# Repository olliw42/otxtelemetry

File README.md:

**LEGACY LEGACY LEGACY**

**This repository is legacy and deprecated.**

Please see https://github.com/olliw42/mTX for the current location of the project and the OlliW Telemetry for mTx Lua script.

-----------

OlliW Telemetry for OpenTx/EdgeTx with MAVLink, Lua Scripts, Hardware, Code and Stuff
===========

The project brings native MAVLink telemetry capabilities to OpenTx.

Project home page: http://www.olliw.eu/2020/olliwtelem

Discussion thread at rcgroups: https://www.rcgroups.com/forums/showthread.php?3532969-MAVLink-for-OpenTx-and-Telemetry-Script

## Lua Widget Scripts: Installation

The latest telemetry script works with OpenTx (for EdgeTx only "older" firmwares/scripts are available).

For the moment please visit the project web page for descriptions, or better, join the discussion thread.

## External Transmitter Bay MAVLink Bridge

For the moment please visit the discussion thread.

## Licence

GPL v3

## Acknowledgements

The design of the autopilot page is much inspired by the Yaapu Telemetry script. (https://github.com/yaapu/FrskyTelemetryScript)

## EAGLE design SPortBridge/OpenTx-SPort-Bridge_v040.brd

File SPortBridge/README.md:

OlliW Telemetry for OpenTx/EdgeTx with MAVLink: SPort Bridge
===========

The SPort Bridge translates between the bi-directional one-wire communication signal on the SPort pin and the normal bi-directional two-wire (Tx, Rx) UART signals.

Hardware-wise this requires two functional units, a unit which is doing the splicing from one to two and also inverts the signals, and a microprocessor which decodes/encodes the signal on the one-wire line. 

Comment: The principle is not new at all and widley used. It is e.g. also used in the MPM (multi protocol module) or Siyi FM30 (which just copied it from MNM).

Comment: Microcontroller exist which do provide the slice&invert function internally, which would allow a significantly reduced scheme. The STM32F103, which I use here, does not have that, hence the extra "chicken fat", but I use it since it is also used in the Siyi FM30 transmitter module, which is an excellent commercially available and reasonably priced hardware platform for our purposes. So, the PCB here is actually kind of a development platform for that.

The PCB can be populated such that it exactly reproduces the splicing/inverting unit as used in the MPM and Siyi FM30 (which is normally high level), but it also can be populated such that it is more appropriate for a normally low signal like the one on the SPort (I use that scheme).

The microcontroller needs to be loaded with code, an example C code is provided (you need to spice it up with what it needs to build it).

Comment: I would have loved to provide an Arduino sketch, since this would be really the easiest for most, but I could not figure out how to call low level CMSIS functions in this framework. MAybe some can provide an example or help me out with this.

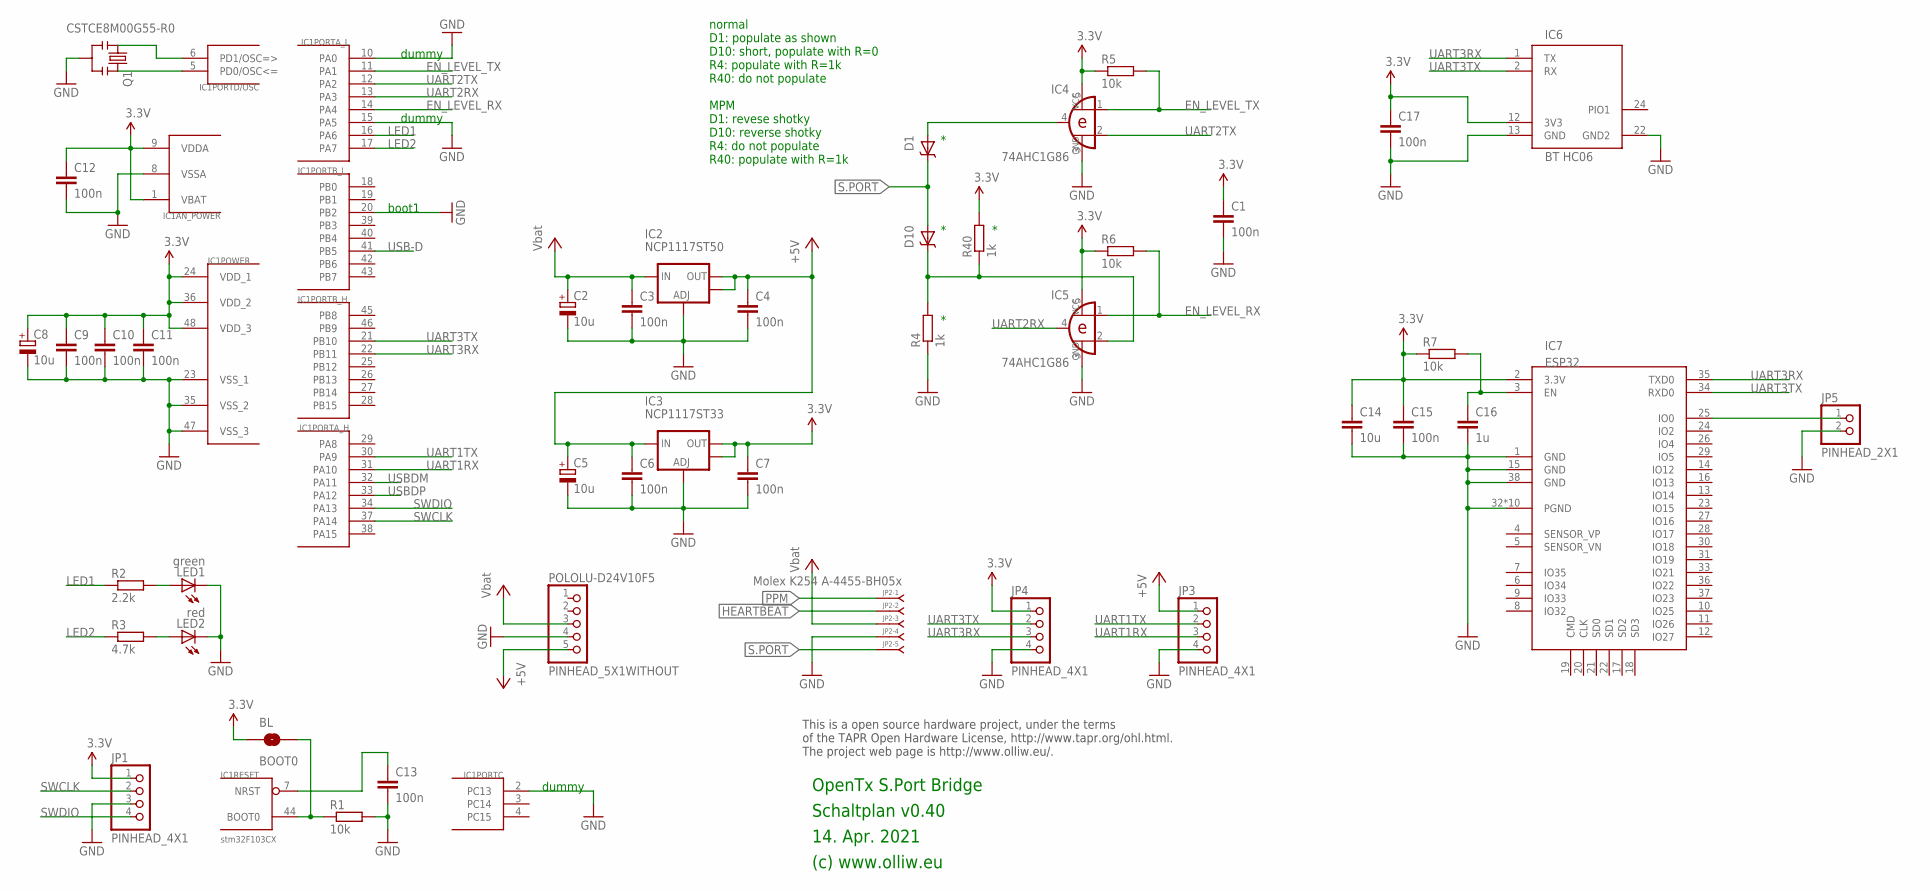
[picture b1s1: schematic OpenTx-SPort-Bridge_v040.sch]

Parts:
BL: BOOT0; SJ_2S-NO
C1, C3, C4, C6, C7, C9, C10, C11, C12, C13, C15, C17: 100n; C0603
C2, C5, C8: 10u; SMC_A
C14: 10u; C0805
C16: 1u; C0603
D1, D10: PMEG3010ER; SOD123W-DIODE
IC1: stm32F103CX; TQFP48
IC2: NCP1117ST50; SOT223
IC3: NCP1117ST33; SOT223
IC4, IC5: 74AHC1G86; SOT23-5-VER1
IC6: BT HC06; BT_HC05_BASIC
IC7: ESP32; ESP-WROOM-32D
JP1, JP3, JP4: PINHEAD_4X1
JP2: Molex K254 A-4455-BH05x; 4455-B05
JP5: PINHEAD_2X1
LED1: green; LED3MM
LED2: red; LED3MM
POLOLU-D24V10F5: PINHEAD_5X1WITHOUT; PINHEAD_5X1_WO
Q1: CSTCE8M00G55-R0; RESONATOR-SMD
R1, R5, R6, R7: 10k; R0603
R2: 2.2k; R0603
R3: 4.7k; R0603
R4, R40: 1k; R0603

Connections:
3.3V: BL.1, C1.1, C7.1, C8.+, C9.1, C10.1, C11.1, C12.1, C14.1, C15.1, C17.1, IC1.1 (VBAT), IC1.9 (VDDA), IC1.24 (VDD_1), IC1.36 (VDD_2), IC1.48 (VDD_3), IC3.2 (OUT), IC3.4 (OUT), IC4.5 (VCC), IC5.5 (VCC), IC6.12 (3V3), IC7.2 (3.3V), JP1.1, JP4.1, R5.1, R6.1, R7.1, R40.2
+5V: C4.1, C5.+, C6.1, IC2.2 (OUT), IC2.4 (OUT), IC3.3 (IN), JP3.1, POLOLU-D24V10F5.5
BOOT0: BL.2, IC1.44 (BOOT0), R1.1
EN_LEVEL_RX: IC1.14 (PA4), IC5.1 (I0), R6.2
EN_LEVEL_TX: IC1.11 (PA1), IC4.1 (I0), R5.2
GND: C1.2, C2.-, C3.2, C4.2, C5.-, C6.2, C7.2, C8.-, C9.2, C10.2, C11.2, C12.2, C13.2, C14.2, C15.2, C16.2, C17.2, IC1.2 (PC13), IC1.8 (VSSA), IC1.10 (PA0), IC1.15 (PA5), IC1.20 (PB2), IC1.23 (VSS_1), IC1.35 (VSS_2), IC1.47 (VSS_3), IC2.1 (ADJ), IC3.1 (ADJ), IC4.3 (GND), IC5.3 (GND), IC6.13 (GND), IC6.22 (GND2), IC7.1 (GND), IC7.15 (GND), IC7.32 (PGND), IC7.38 (GND), IC7.39 (PGND), IC7.40 (PGND), IC7.41 (PGND), IC7.42 (PGND), IC7.43 (PGND), IC7.44 (PGND), IC7.45 (PGND), IC7.46 (PGND), IC7.47 (PGND), JP1.3, JP2.4, JP3.4, JP4.4, JP5.2, LED1.K (C), LED2.K (C), POLOLU-D24V10F5.4, Q1.2, R1.2, R4.1
HEARTBEAT: JP2.2
LED1: IC1.16 (PA6), R2.1
LED2: IC1.17 (PA7), R3.1
unnamed: IC7.25 (IO0), JP5.1
unnamed: C16.1, IC7.3 (EN), R7.2
unnamed: D10.C, IC5.2 (I1), R4.2, R40.1
unnamed: D1.A, IC4.4 (O)
unnamed: C13.1, IC1.7 (NRST)
unnamed: LED1.A, R2.2
unnamed: LED2.A, R3.2
unnamed: IC1.5 (PD0/OSC<=), Q1.3
unnamed: IC1.6 (PD1/OSC=>), Q1.1
PPM: JP2.1
S.PORT: D1.C, D10.A, JP2.5
SWCLK: IC1.37 (PA14), JP1.2
SWDIO: IC1.34 (PA13), JP1.4
UART1RX: IC1.31 (PA10), JP3.3
UART1TX: IC1.30 (PA9), JP3.2
UART2RX: IC1.13 (PA3), IC5.4 (O)
UART2TX: IC1.12 (PA2), IC4.2 (I1)
UART3RX: IC1.22 (PB11), IC6.1 (TX), IC7.35 (TXD0), JP4.3
UART3TX: IC1.21 (PB10), IC6.2 (RX), IC7.34 (RXD0), JP4.2
USB-D: IC1.41 (PB5)
USBDM: IC1.32 (PA11)
USBDP: IC1.33 (PA12)
VCC: C2.+, C3.1, IC2.3 (IN), JP2.3, POLOLU-D24V10F5.3

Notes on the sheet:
14. Apr. 2021
(c) www.olliw.eu
OpenTx S.Port Bridge
Schaltplan v0.40
This is a open source hardware project, under the terms of the TAPR Open Hardware License, http://www.tapr.org/ohl.html. The project web page is http://www.olliw.eu/.
boot1
normal D1: populate as shown D10: short, populate with R=0 R4: populate with R=1k R40: do not populate MPM D1: revese shotky D10: reverse shotky R4: do not populate R40: populate with R=1k
dummy

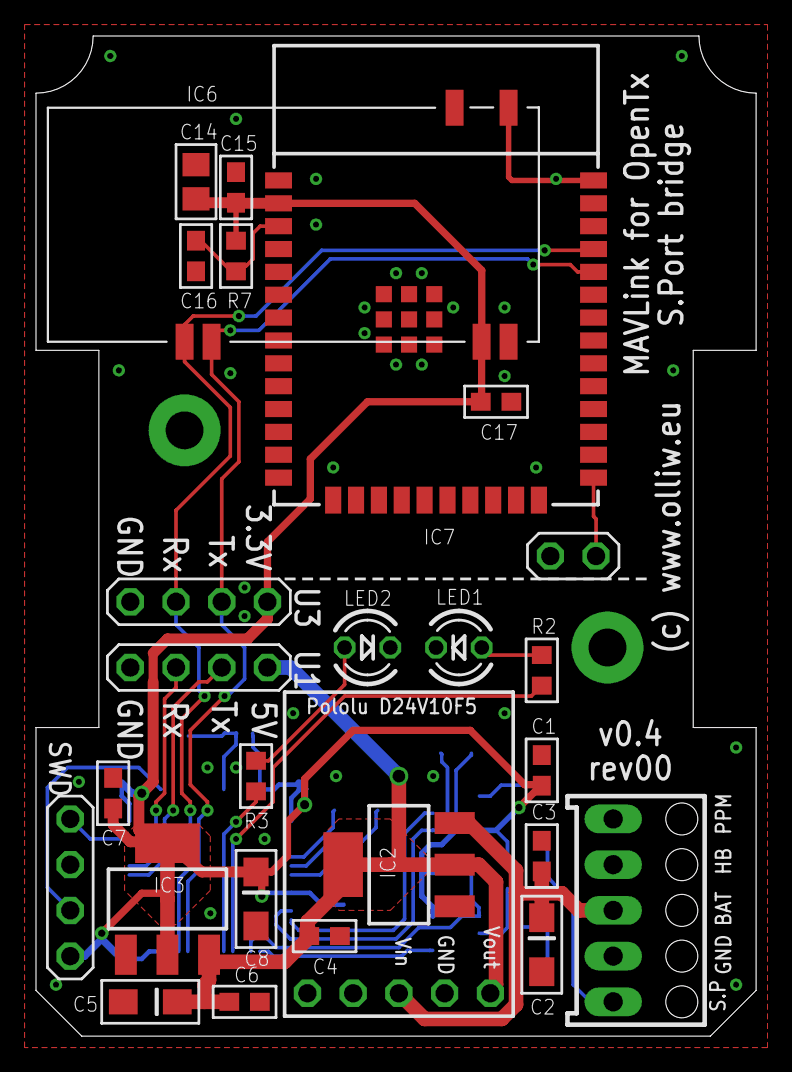
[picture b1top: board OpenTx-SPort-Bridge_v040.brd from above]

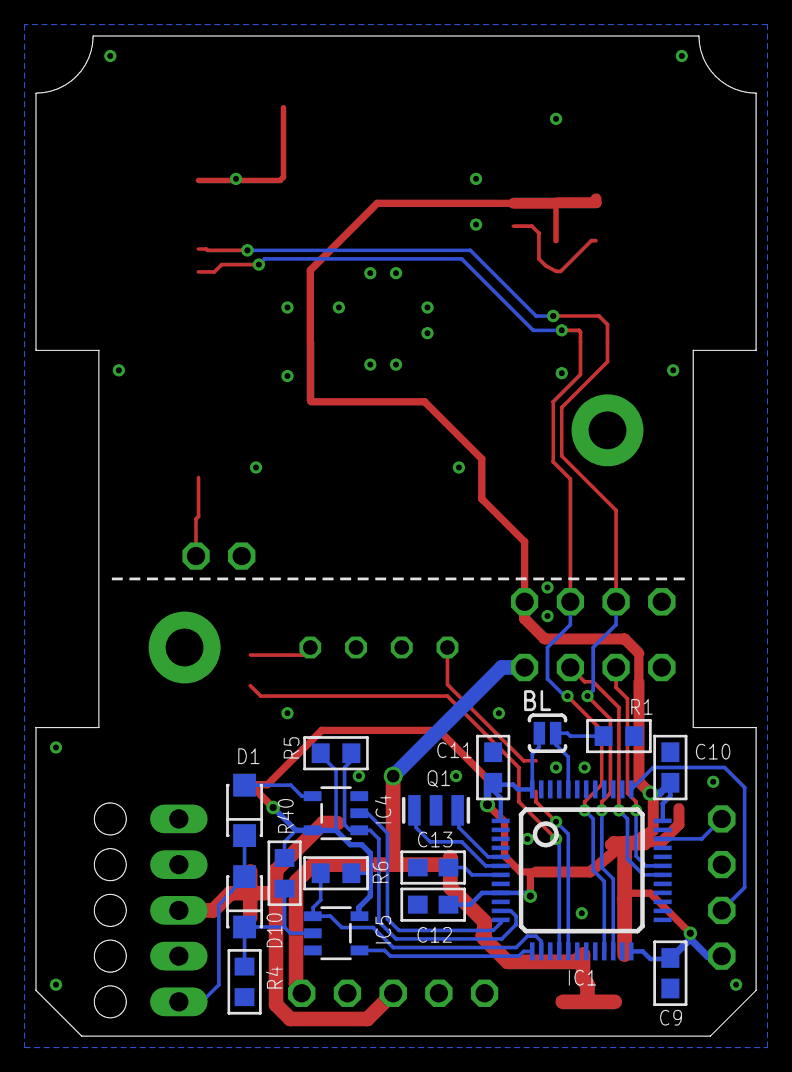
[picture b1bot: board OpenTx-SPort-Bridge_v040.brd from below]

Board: 2 copper layers, 40.0 x 55.6 mm, 44 parts (17 on the bottom side), 27 nets.

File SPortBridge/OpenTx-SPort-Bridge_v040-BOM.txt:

Stückliste exportiert aus C:/Users/Olli/Documents/GitHub/otxtelemetry/SPortBridge/OpenTx-SPort-Bridge_v040.sch am 10.06.2021 18:21

Part            Value                   Device                 Package        Description                          
BL              BOOT0                   SOLDERJUMPERNO         SJ_2S-NO       Solder Jumper                        
C1              100n                    C-EUC0603              C0603          CAPACITOR, European symbol           
C2              10u                     CPOL-EUSMCA            SMC_A          POLARIZED CAPACITOR, European symbol 
C3              100n                    C-EUC0603              C0603          CAPACITOR, European symbol           
C4              100n                    C-EUC0603              C0603          CAPACITOR, European symbol           
C5              10u                     CPOL-EUSMCA            SMC_A          POLARIZED CAPACITOR, European symbol 
C6              100n                    C-EUC0603              C0603          CAPACITOR, European symbol           
C7              100n                    C-EUC0603              C0603          CAPACITOR, European symbol           
C8              10u                     CPOL-EUSMCA            SMC_A          POLARIZED CAPACITOR, European symbol 
C9              100n                    C-EUC0603              C0603          CAPACITOR, European symbol           
C10             100n                    C-EUC0603              C0603          CAPACITOR, European symbol           
C11             100n                    C-EUC0603              C0603          CAPACITOR, European symbol           
C12             100n                    C-EUC0603              C0603          CAPACITOR, European symbol           
C13             100n                    C-EUC0603              C0603          CAPACITOR, European symbol           
C14             10u                     C-EUC0805              C0805          CAPACITOR, European symbol           
C15             100n                    C-EUC0603              C0603          CAPACITOR, European symbol           
C16             1u                      C-EUC0603              C0603          CAPACITOR, European symbol           
C17             100n                    C-EUC0603              C0603          CAPACITOR, European symbol           
D1              PMEG3010ER              DIODE-SCHOTTKYSOD123-W SOD123W-DIODE                                       
D10             PMEG3010ER              DIODE-SCHOTTKYSOD123-W SOD123W-DIODE                                       
IC1             stm32F103CX             STM32F10XCXT6          TQFP48         ST STM32F101/103 48pin LQFP          
IC2             NCP1117ST50             V_REG_LM1117SOT223     SOT223         Voltage Regulator LM1117             
IC3             NCP1117ST33             V_REG_LM1117SOT223     SOT223         Voltage Regulator LM1117             
IC4             74AHC1G86               74AHC1G86              SOT23-5-VER1                                        
IC5             74AHC1G86               74AHC1G86              SOT23-5-VER1                                        
IC6             BT HC06                 HC06-BASIC             BT_HC05_BASIC                                       
IC7             ESP32                   ESP32                  ESP-WROOM-32D                                       
JP1             PINHEAD_4X1             PINHEAD_4X1            PINHEAD_4X1                                         
JP2             Molex K254 A-4455-BH05x 4455-B05_S             4455-B05       RECEPTACAL                           
JP3             PINHEAD_4X1             PINHEAD_4X1            PINHEAD_4X1                                         
JP4             PINHEAD_4X1             PINHEAD_4X1            PINHEAD_4X1                                         
JP5             PINHEAD_2X1             PINHEAD_2X1            PINHEAD_2X1                                         
LED1            green                   LED3MM                 LED3MM         LED                                  
LED2            red                     LED3MM                 LED3MM         LED                                  
POLOLU-D24V10F5 PINHEAD_5X1WITHOUT      PINHEAD_5X1WITHOUT     PINHEAD_5X1_WO                                      
Q1              CSTCE8M00G55-R0         RESONATORSMD           RESONATOR-SMD  Resonator                            
R1              10k                     R-EU_R0603             R0603          RESISTOR, European symbol            
R2              2.2k                    R-EU_R0603             R0603          RESISTOR, European symbol            
R3              4.7k                    R-EU_R0603             R0603          RESISTOR, European symbol            
R4              1k                      R-EU_R0603             R0603          RESISTOR, European symbol            
R5              10k                     R-EU_R0603             R0603          RESISTOR, European symbol            
R6              10k                     R-EU_R0603             R0603          RESISTOR, European symbol            
R7              10k                     R-EU_R0603             R0603          RESISTOR, European symbol            
R40             1k                      R-EU_R0603             R0603          RESISTOR, European symbol

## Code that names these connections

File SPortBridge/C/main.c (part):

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#define SPORT_UART    UART2
#define SPORT_BAUD    400000

#define SPORT_TX_EN_LEVEL_GPIO   PA1
#define SPORT_RX_EN_LEVEL_GPIO   PA4

#define SERIAL_UART   USART1
#define SERIAL_BAUD   57600
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#define SERIAL2_UART  UART3
#define SERIAL2_BAUD  57600

#define LED_GPIO      PA7
#define LED2_GPIO     PA6
*/


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
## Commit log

2020-02-14 readme initial
2020-02-14 SD card initial
2020-02-14 main initial
2020-02-14 main.lua, firmware, initial
2020-02-14 v0.0.4 inital
2020-02-17 firmware v02 2020-02-17
2020-02-23 flightmodes updated
2020-02-23 arned/disarmed sound
2020-02-23 improved pages, quickshot page template added
2020-02-24 updated sounds
2020-02-26 status text, mavtelemIsEnabled, and more quickshot
2020-02-26 nomtel sound
2020-02-26 tidy
2020-03-07 guided tests
2020-03-07 cablecam tests
2020-03-08 remove superflous lua files
2020-03-11 position fix sound
2020-03-11 version bump v0.1.0, seems to work great
2020-03-15 v03 2020 03 15
2020-03-30 quickshot readme
2020-03-30 update sd card sound files
2020-03-30 add quickshot script
2020-03-30 resetBacklightTimeout()
2020-03-30 drawIsInitializing()
2020-03-30 v05 2020-03-30
2020-03-31 firmware update to v06
2020-04-01 v07 lcd functions, speeds up script quite a lot
2020-04-01 gimbal rate limit
2020-04-01 update cablecam script, tested
2020-04-01 update firmware to v07
2020-04-03 update firmware to v08
2020-06-07 update firmware to v11
2020-06-09 add latest opentx firmware bin
2020-10-11 update opentx firmware to v16
2020-10-11 update script to match firmware v16
2020-10-11 version bump
2020-12-06 add convenience copy batch file
2020-12-06 qshot, v18 2020-12-06, flight tested
2021-03-12 Fix script getting disabled, when rssi is nil
2021-03-22 update v26 with SDCard content
2021-03-24 for v26rc02
2021-03-24 Debug screen without obstruction
    In order for the debug screen to not overlay the [I]no telemetry[/I] message to be able to see the content when telemetry is not (yet) active.
    I tested this change on my radio, now shows also all stats without overlay, when telemetry is not yet active.
2021-03-24 add debug page, v0.27.1.rc02
2021-03-27 v0.27.0.rc05
2021-06-10 remove & move files
2021-06-10 v27, new main, new firmware binaries
2021-06-10 release SPortBridge v040
2021-06-10 sport bridge, add readme, c code and binary
2021-06-11 text
2021-06-13 add STL files for transmitter bay box
2021-06-18 lua script for v28, slight correction for tx16s
2021-06-20 add .bin
2021-06-22 so it works also for Risto's chip LOL
2021-06-24 v29 firmware binaries
2021-07-06 v30rc06
2021-07-07 make it better clear that the script works for both opentx and edgetx mavlink firmwares
2021-07-24 v30 opentx 2.3.14 edgetx 2.4.0
2021-07-24 wrong touch events greeped in
2021-07-24 v30 again
2021-11-17 quite massive revamp of code structure, lots of libraries now
2021-11-20 sync with new gps driver
2021-11-21 bits and pieces
2022-01-09 lua mbridge
2022-03-11 mbridge rssi LQ
2022-05-05 some debug stuff
2022-05-05 add rover modes, tentative

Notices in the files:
parts and their libraries:
Licensing: CC v3.0 Share-Alike You are welcome to use this library for commercial purposes.
con-molex-kk: Copyright (C) 2010, Bob Starr
